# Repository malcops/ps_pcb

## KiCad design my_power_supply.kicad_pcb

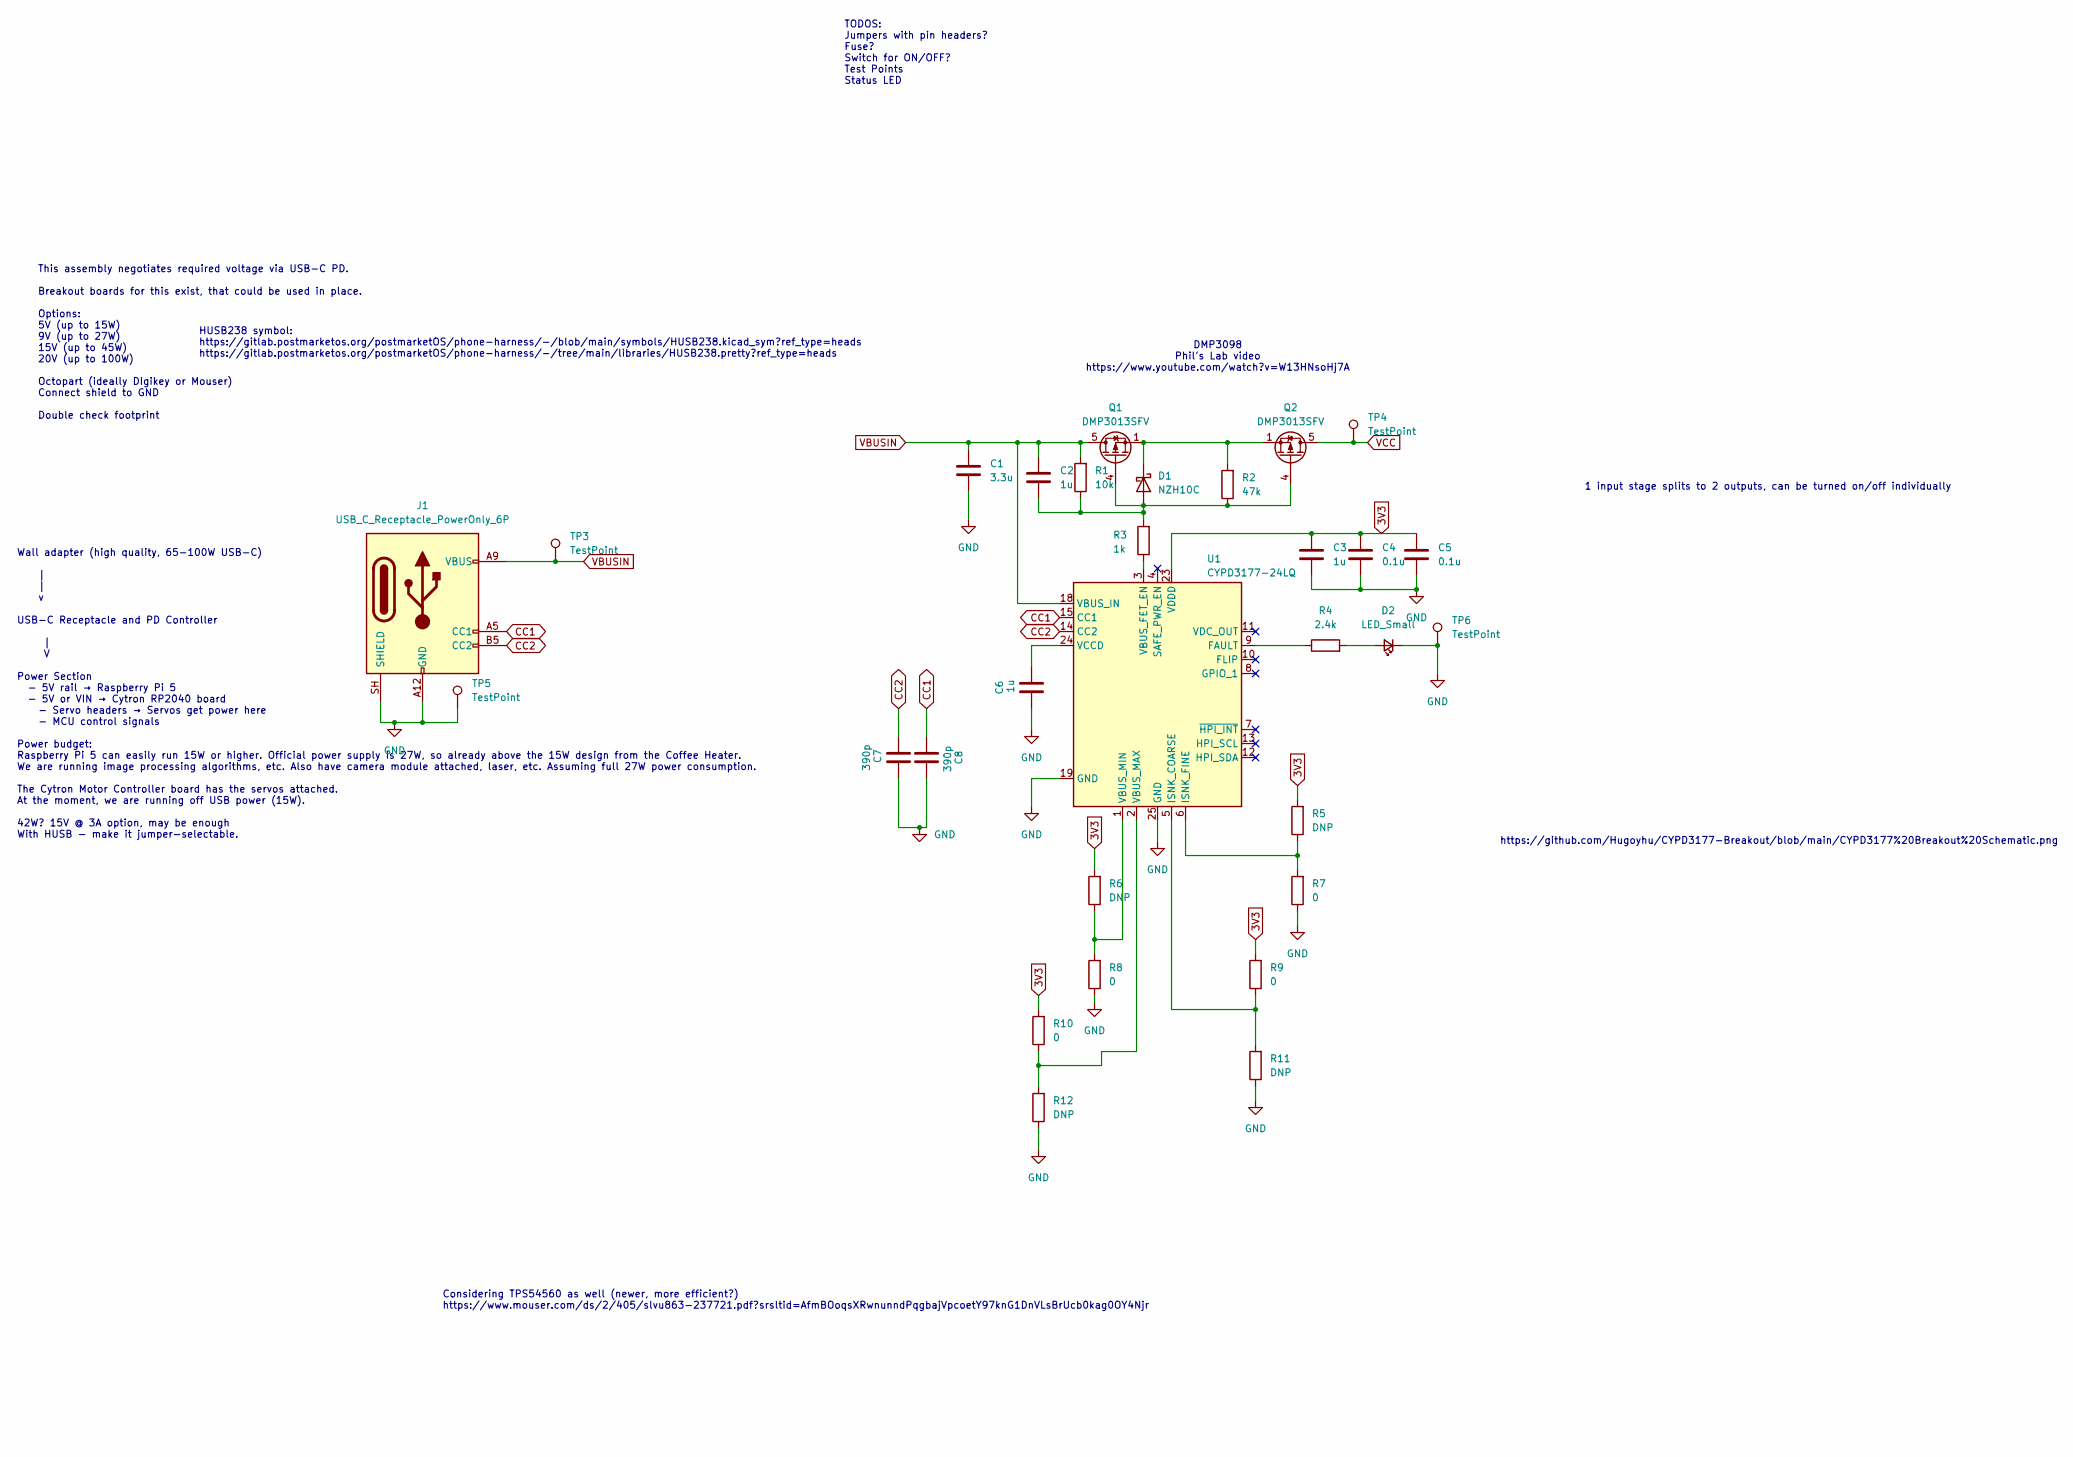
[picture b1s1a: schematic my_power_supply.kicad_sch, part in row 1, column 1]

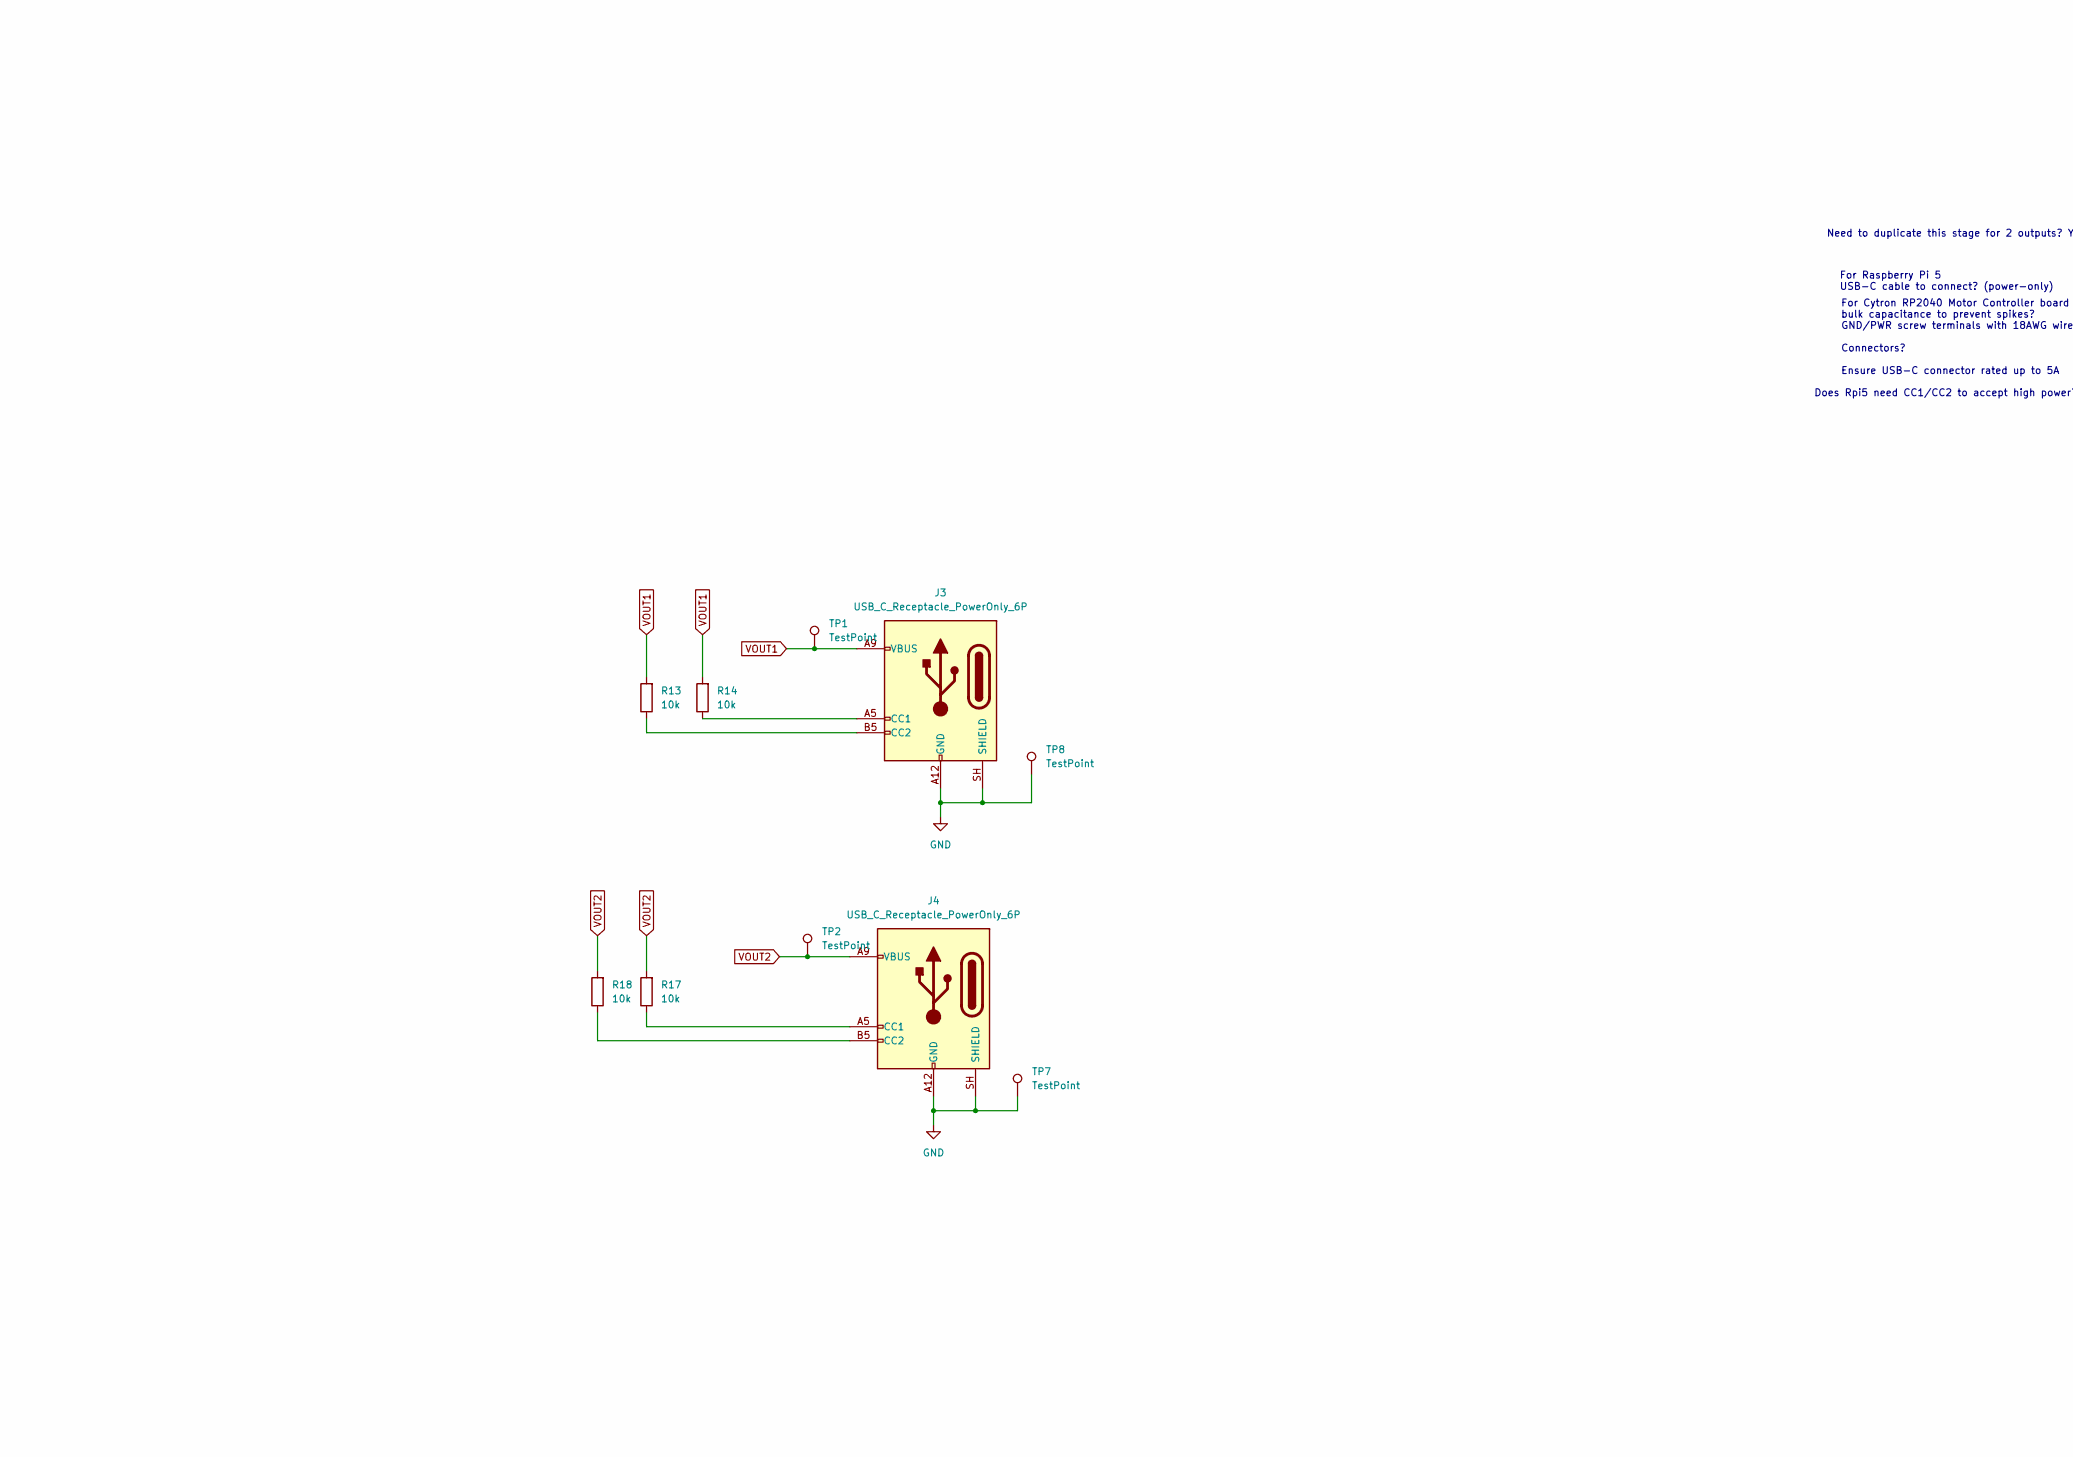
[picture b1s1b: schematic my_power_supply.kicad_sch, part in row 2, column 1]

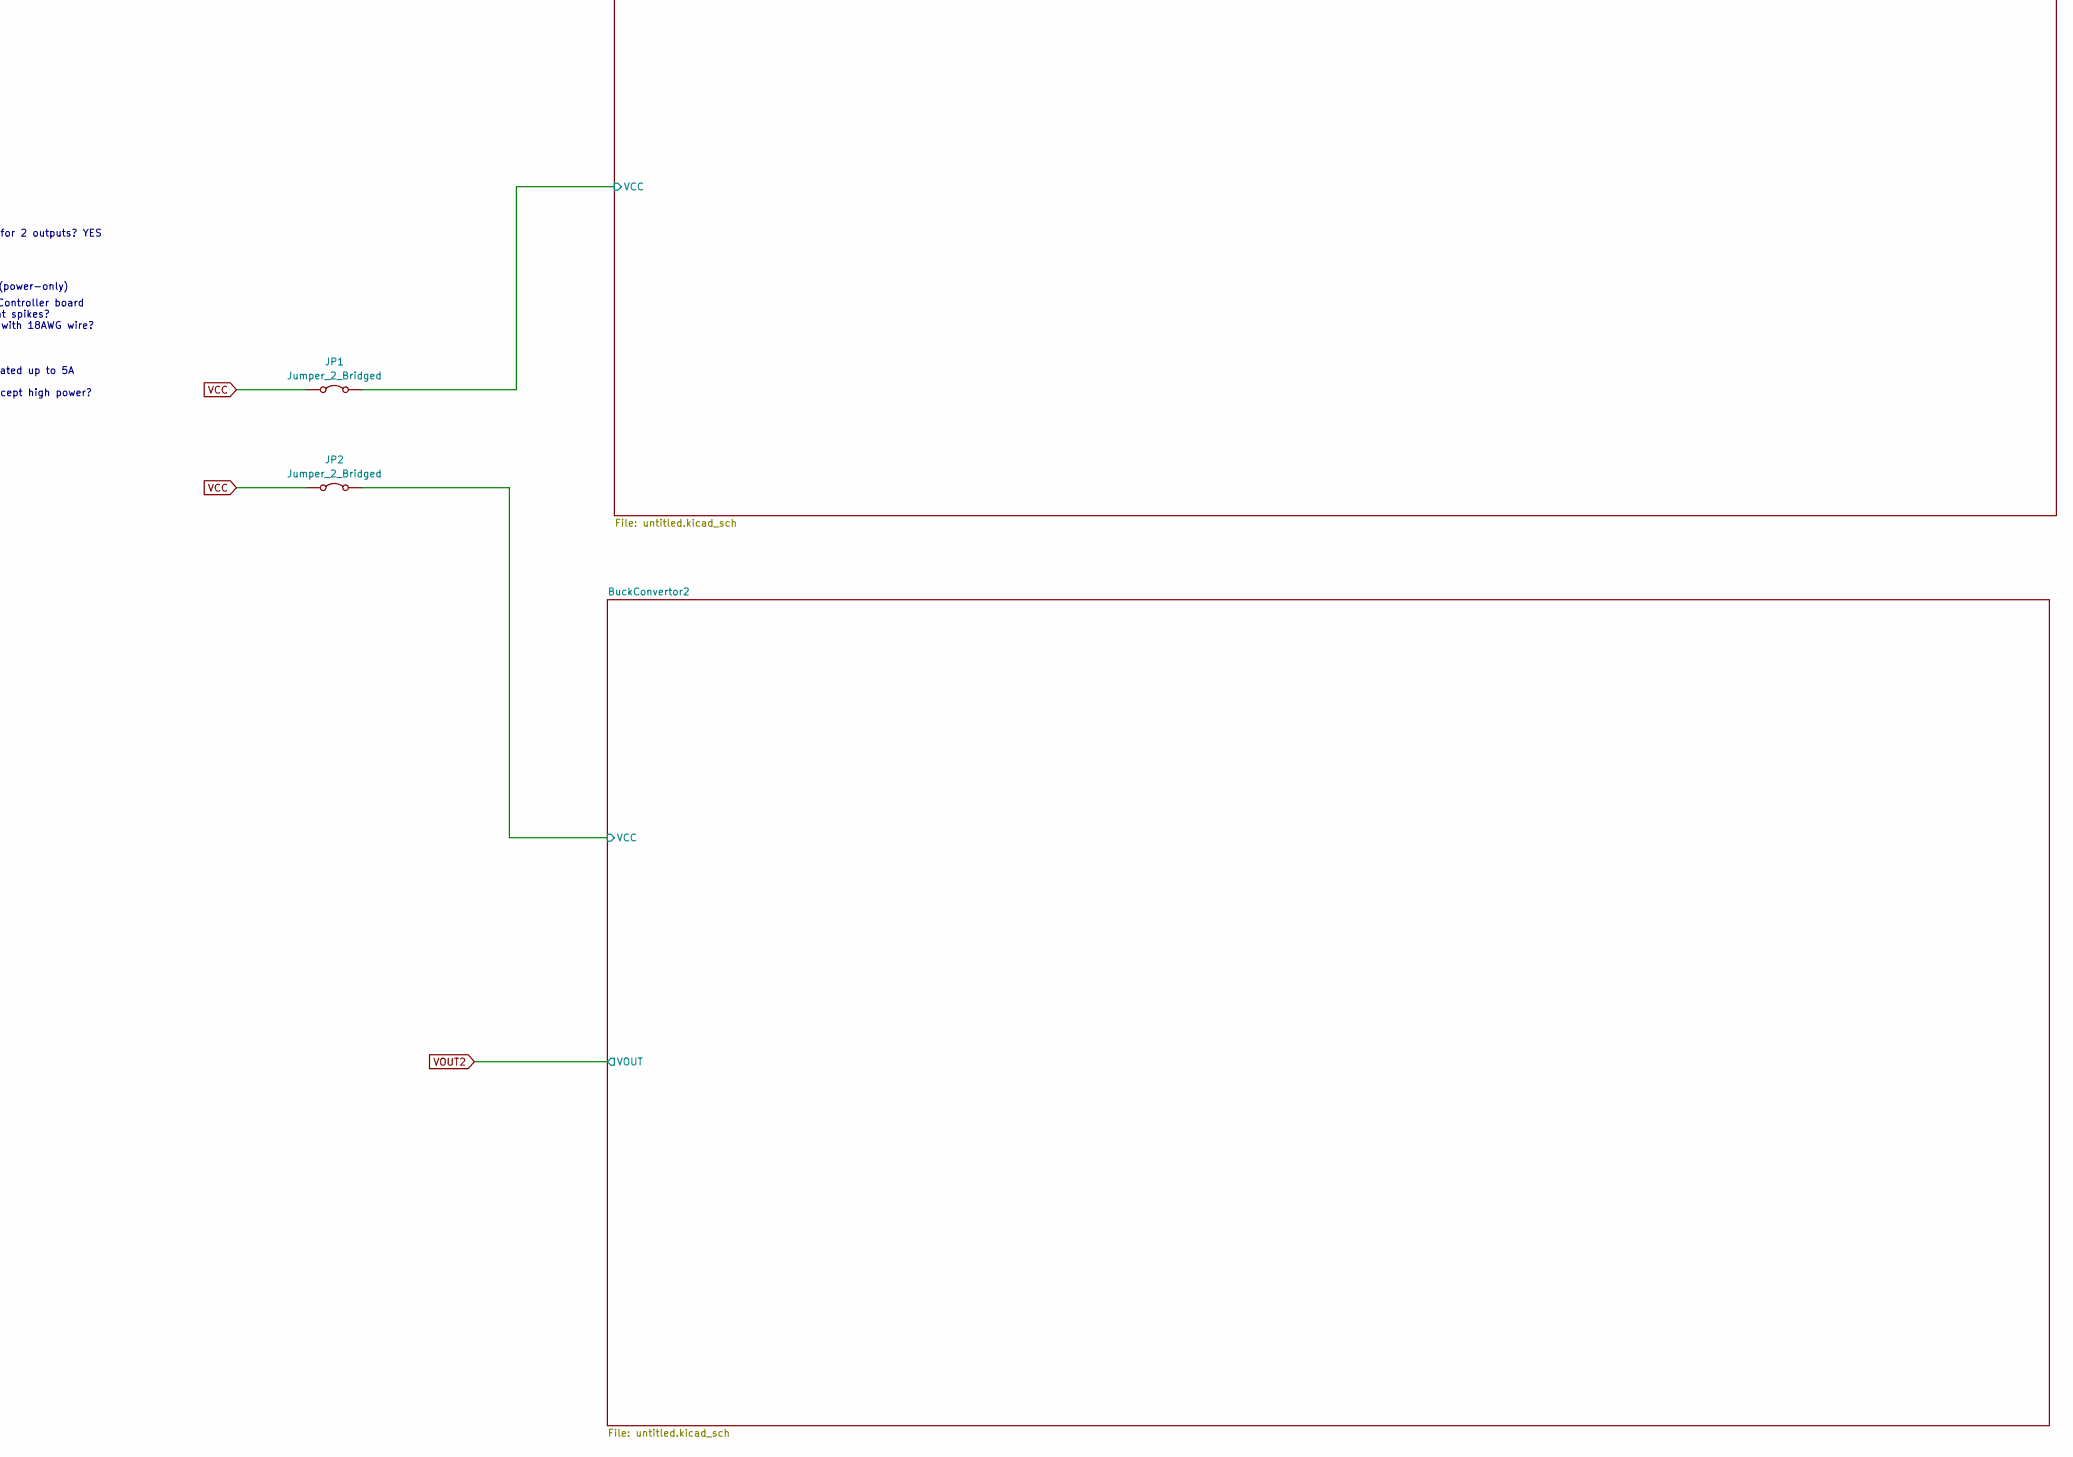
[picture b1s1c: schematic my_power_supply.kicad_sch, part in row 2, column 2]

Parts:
C1: 3.3u; C_1206_3216Metric
C2, C3, C6: 1u; C_1206_3216Metric
C4, C5: 0.1u; C_1206_3216Metric
C7, C8: 390p; C_1206_3216Metric
D1: NZH10C; D_SOD-323F
D2: LED_Small; LED_1206_3216Metric_Pad1.42x1.75mm_HandSolder
J1, J3, J4: USB_C_Receptacle_PowerOnly_6P; USB_C_Receptacle_HRO_TYPE-C-31-M-17
JP1, JP2: Jumper_2_Bridged; PinHeader_1x02_P2.54mm_Vertical
Q1, Q2: DMP3013SFV; Diodes_PowerDI3333-8
R1, R13, R14, R17, R18: 10k; R_1206_3216Metric
R2: 47k; R_1206_3216Metric
R3: 1k; R_1206_3216Metric
R4: 2.4k; R_1206_3216Metric
R5, R6: DNP; R_0805_2012Metric
R7, R8, R9, R10: 0; R_1206_3216Metric
R11, R12: DNP; R_1206_3216Metric
TP1, TP2, TP3, TP4, TP5, TP6, TP7, TP8: TestPoint; TestPoint_Loop_D2.50mm_Drill1.0mm_LowProfile
U1: CYPD3177-24LQ; QFN-24-1EP_4x4mm_P0.5mm_EP2.75x2.75mm

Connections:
3V3: C3.1, C4.1, C5.1, R5.2, R6.2, R9.2, R10.2, U1.23 (VDDD)
/BuckConvertor1/VCC: JP1.2 (B); also elsewhere on the board
/BuckConvertor2/VCC: JP2.2 (B); also elsewhere on the board
CC1: C8.1, J1.A5 (CC1), U1.15 (CC1)
CC2: C7.1, J1.B5 (CC2), U1.14 (CC2)
GND: C1.2, C3.2, C4.2, C5.2, C6.1, C7.2, C8.2, D2.1 (K), J1.A12 (GND), J1.B12 (GND), J1.SH (SHIELD), J3.A12 (GND), J3.B12 (GND), J3.SH (SHIELD), J4.A12 (GND), J4.B12 (GND), J4.SH (SHIELD), R7.1, R8.1, R11.1, R12.1, TP5.1 (1_1), TP6.1 (1_1), TP7.1 (1_1), TP8.1 (1_1), U1.19 (GND), U1.22 (GND), U1.25 (GND); also elsewhere on the board
unnamed: C2.2, D1.2 (A), Q1.4 (G), Q2.4 (G), R1.1, R2.1, R3.2
unnamed: D1.1 (K), Q1.1 (S), Q1.2 (S), Q1.3 (S), Q2.1 (S), Q2.2 (S), Q2.3 (S), R2.2
unnamed: D2.2 (A), R4.2
unnamed: J3.A5 (CC1), R14.1
unnamed: J3.B5 (CC2), R13.1
unnamed: J4.A5 (CC1), R17.1
unnamed: J4.B5 (CC2), R18.1
unnamed: R4.1, U1.9 (FAULT)
unnamed: R9.1, R11.2, U1.5 (ISNK_COARSE)
unnamed: R5.1, R7.2, U1.6 (ISNK_FINE)
unnamed: R3.1, U1.3 (VBUS_FET_EN)
unnamed: R10.1, R12.2, U1.2 (VBUS_MAX)
unnamed: R6.1, R8.2, U1.1 (VBUS_MIN)
unnamed: C6.2, U1.24 (VCCD)
VBUSIN: C1.1, C2.1, J1.A9 (VBUS), J1.B9 (VBUS), Q1.5 (D), R1.2, TP3.1 (1_1), U1.18 (VBUS_IN)
VCC: JP1.1 (A), JP2.1 (A), Q2.5 (D), TP4.1 (1_1)
VOUT1: J3.A9 (VBUS), J3.B9 (VBUS), R13.2, R14.2, TP1.1 (1_1); also elsewhere on the board
VOUT2: J4.A9 (VBUS), J4.B9 (VBUS), R17.2, R18.2, TP2.1 (1_1); also elsewhere on the board

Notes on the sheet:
Does Rpi5 need CC1/CC2 to accept high power?
https://github.com/Hugoyhu/CYPD3177-Breakout/blob/main/CYPD3177%20Breakout%20Schematic.png
TODOS: Jumpers with pin headers? Fuse? Switch for ON/OFF? Test Points Status LED
Considering TPS54560 as well (newer, more efficient?) https://www.mouser.com/ds/2/405/slvu863-237721.pdf?srsltid=AfmBOoqsXRwnunndPqgbajVpcoetY97knG1DnVLsBrUcb0kag0OY4Njr
This assembly negotiates required voltage via USB-C PD. Breakout boards for this exist, that could be used in place. Options: 5V (up to 15W) 9V (up to 27W) 15V (up to 45W) 20V (up to 100W) Octopart (ideally DIgikey or Mouser) Connect shield to GND Double check footprint
Need to duplicate this stage for 2 outputs? YES
HUSB238 symbol: https://gitlab.postmarketos.org/postmarketOS/phone-harness/-/blob/main/symbols/HUSB238.kicad_sym?ref_type=heads https://gitlab.postmarketos.org/postmarketOS/phone-harness/-/tree/main/libraries/HUSB238.pretty?ref_type=heads
Wall adapter (high quality, 65-100W USB-C) | | v USB-C Receptacle and PD Controller | V Power Section - 5V rail → Raspberry Pi 5 - 5V or VIN → Cytron RP2040 board - Servo headers → Servos get power here - MCU control signals Power budget: Raspberry Pi 5 can easily run 15W or higher. Official power 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
For Raspberry Pi 5 USB-C cable to connect? (power-only)
1 input stage splits to 2 outputs, can be turned on/off individually
DMP3098 Phil's Lab video https://www.youtube.com/watch?v=W13HNsoHj7A
For Cytron RP2040 Motor Controller board bulk capacitance to prevent spikes? GND/PWR screw terminals with 18AWG wire? Connectors? Ensure USB-C connector rated up to 5A

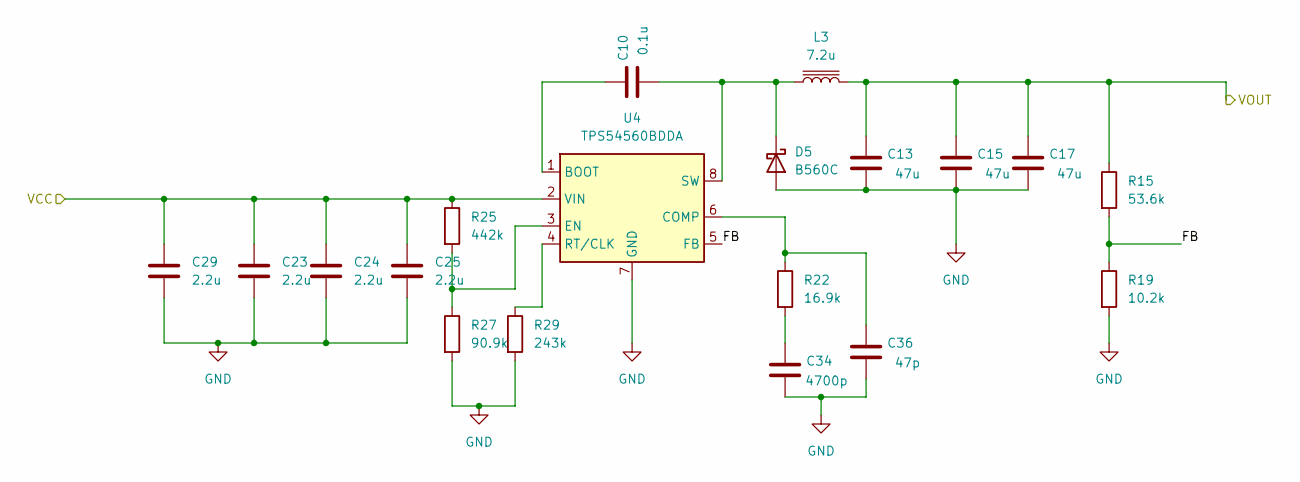
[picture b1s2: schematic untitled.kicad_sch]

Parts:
C10: 0.1u; C_1206_3216Metric
C13, C15, C17: 47u; C_1206_3216Metric
C23, C24, C25, C29: 2.2u; C_1206_3216Metric
C34: 4700p; C_1206_3216Metric
C36: 47p; C_1206_3216Metric
D5: B560C; SMC_DIO
L3: 7.2u; L_Wurth_WE-PDF-1045
R15: 53.6k; R_1206_3216Metric
R19: 10.2k; R_1206_3216Metric
R22: 16.9k; R_1206_3216Metric
R25: 442k; R_1206_3216Metric
R27: 90.9k; R_1206_3216Metric
R29: 243k; R_1206_3216Metric
U4: TPS54560BDDA; Texas_R-PDSO-G8_EP2.95x4.9mm_Mask2.4x3.1mm_ThermalVias

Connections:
/BuckConvertor1/FB: R15.2, R19.1, U4.5 (FB)
/BuckConvertor1/VCC: C23.1, C24.1, C25.1, C29.1, R25.1, U4.2 (VIN); also elsewhere on the board
GND: C13.1, C15.1, C17.1, C23.2, C24.2, C25.2, C29.2, C34.1, C36.1, D5.2 (A), R19.2, R27.2, R29.2, U4.7 (GND), U4.9 (GND); also elsewhere on the board
unnamed: C34.2, R22.2
unnamed: C10.1, D5.1 (K), L3.1, U4.8 (SW)
unnamed: C10.2, U4.1 (BOOT)
unnamed: C36.2, R22.1, U4.6 (COMP)
unnamed: R25.2, R27.1, U4.3 (EN)
unnamed: R29.1, U4.4 (RT/CLK)
VOUT1: C13.2, C15.2, C17.2, L3.2, R15.1; also elsewhere on the board

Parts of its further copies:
C11: 0.1u; C_1206_3216Metric
C14, C16, C18: 47u; C_1206_3216Metric
C30, C31, C32, C33: 2.2u; C_1206_3216Metric
C35: 4700p; C_1206_3216Metric
C37: 47p; C_1206_3216Metric
D6: B560C; SMC_DIO
L4: 7.2u; L_Wurth_WE-PDF-1045
R16: 53.6k; R_1206_3216Metric
R20: 10.2k; R_1206_3216Metric
R23: 16.9k; R_1206_3216Metric
R26: 442k; R_1206_3216Metric
R28: 90.9k; R_1206_3216Metric
R30: 243k; R_1206_3216Metric
U5: TPS54560BDDA; Texas_R-PDSO-G8_EP2.95x4.9mm_Mask2.4x3.1mm_ThermalVias

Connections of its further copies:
/BuckConvertor2/FB: R16.2, R20.1, U5.5 (FB)
/BuckConvertor2/VCC: C30.1, C31.1, C32.1, C33.1, R26.1, U5.2 (VIN); also elsewhere on the board
GND: C14.1, C16.1, C18.1, C30.2, C31.2, C32.2, C33.2, C35.1, C37.1, D6.2 (A), R20.2, R28.2, R30.2, U5.7 (GND), U5.9 (GND); also elsewhere on the board
unnamed: C35.2, R23.2
unnamed: C11.1, D6.1 (K), L4.1, U5.8 (SW)
unnamed: C11.2, U5.1 (BOOT)
unnamed: C37.2, R23.1, U5.6 (COMP)
unnamed: R26.2, R28.1, U5.3 (EN)
unnamed: R30.1, U5.4 (RT/CLK)
VOUT2: C14.2, C16.2, C18.2, L4.2, R16.1; also elsewhere on the board

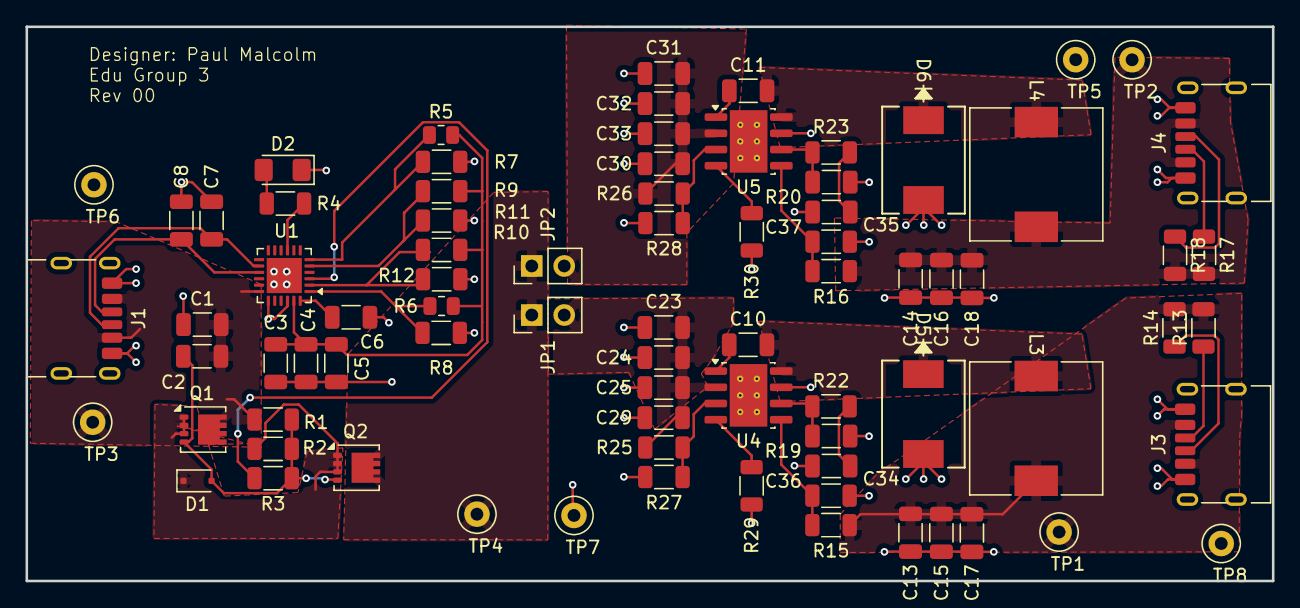
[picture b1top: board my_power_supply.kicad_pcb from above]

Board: 2 copper layers, 97.6 x 43.4 mm, 80 parts (0 on the bottom side), 38 nets.
